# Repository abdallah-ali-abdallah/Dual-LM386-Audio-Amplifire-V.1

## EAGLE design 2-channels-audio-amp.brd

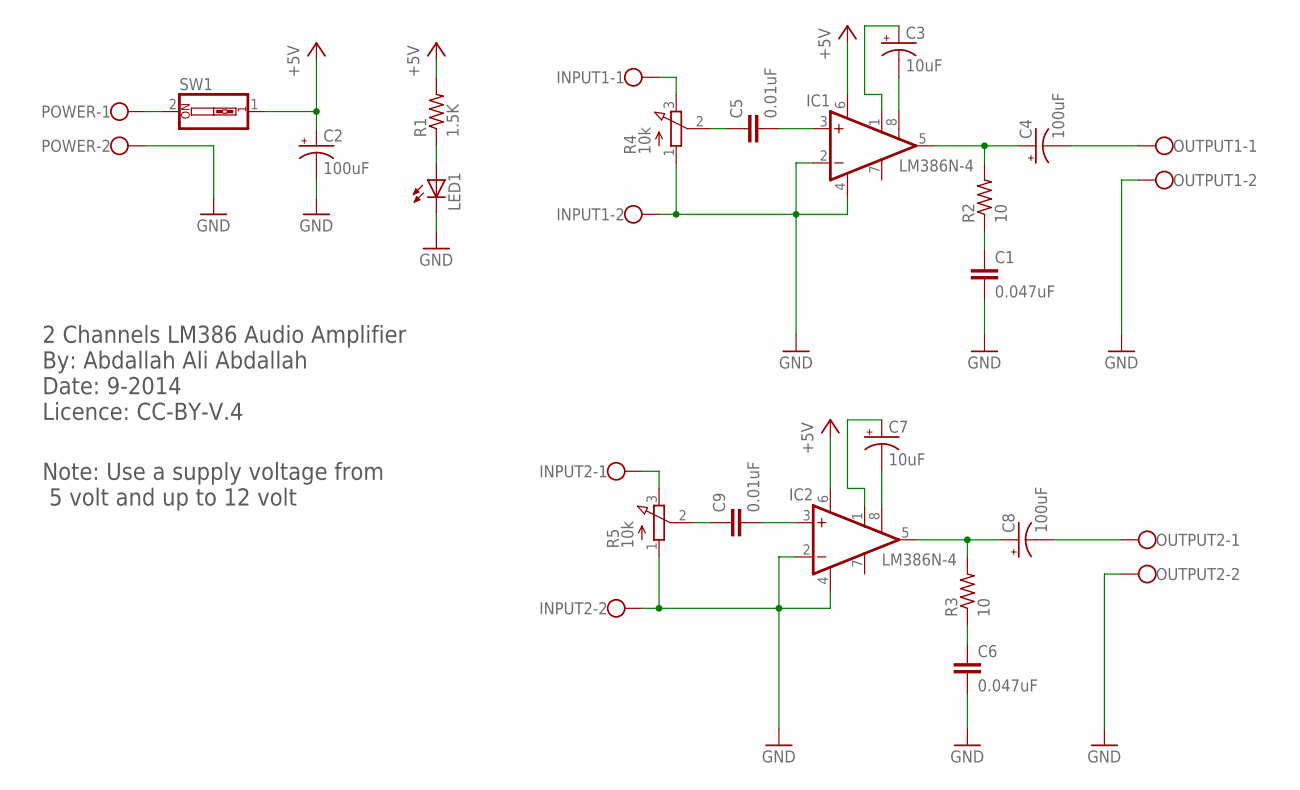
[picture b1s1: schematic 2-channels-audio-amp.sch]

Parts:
C1, C6: 0.047uF; C025-025X050
C2, C4, C8: 100uF; E2,5-6
C3, C7: 10uF; E2,5-6
C5, C9: 0.01uF; C025-025X050
IC1, IC2: LM386N-4; DIL08
INPUT1, INPUT2: W237-102
LED1: LED5MM
OUTPUT1, OUTPUT2: W237-102
POWER: W237-102
R1: 1.5K; 0204/7
R2, R3: 10; 0204/7
R4, R5: 10k; 3RP/1610N
SW1: SW_DIP-1; EDG-01

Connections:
+5V: C2.+, IC1.6 (VS), IC2.6 (VS), R1.2, SW1.1
GND: C1.2, C2.-, C6.2, IC1.2 (-IN), IC1.4 (GND), IC2.2 (-IN), IC2.4 (GND), INPUT1.2, INPUT2.2, LED1.K (C), OUTPUT1.2, OUTPUT2.2, POWER.2, R4.1 (A), R5.1 (A)
unnamed: C4.+, IC1.5 (OUT), R2.2
unnamed: C3.-, IC1.8 (GAIN)
unnamed: C3.+, IC1.1 (GAIN)
unnamed: C4.-, OUTPUT1.1
unnamed: C1.1, R2.1
unnamed: INPUT1.1, R4.3 (E)
unnamed: LED1.A, R1.1
unnamed: C5.2, IC1.3 (+IN)
unnamed: C7.-, IC2.8 (GAIN)
unnamed: C7.+, IC2.1 (GAIN)
unnamed: POWER.1, SW1.2
unnamed: C8.+, IC2.5 (OUT), R3.2
unnamed: C8.-, OUTPUT2.1
unnamed: C6.1, R3.1
unnamed: C9.2, IC2.3 (+IN)
unnamed: INPUT2.1, R5.3 (E)
unnamed: C5.1, R4.2 (S)
unnamed: C9.1, R5.2 (S)

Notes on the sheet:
2 Channels LM386 Audio Amplifier By: Abdallah Ali Abdallah Date: 9-2014 Licence: CC-BY-V.4
Note: Use a supply voltage from 5 volt and up to 12 volt

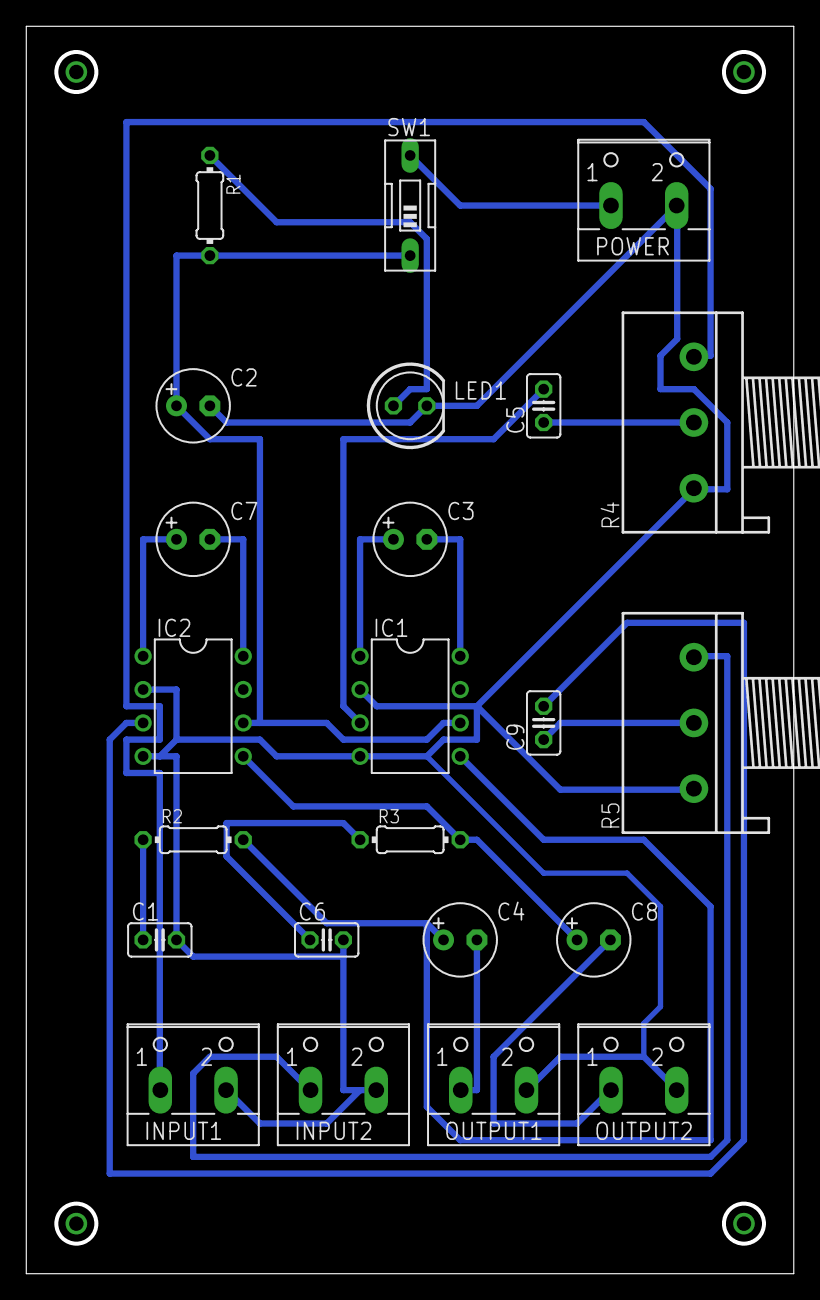
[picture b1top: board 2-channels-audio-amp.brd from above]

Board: 2 copper layers, 58.1 x 94.6 mm, 23 parts (0 on the bottom side), 20 nets.

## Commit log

2014-09-14 :tada: Added .gitattributes & .gitignore files
2014-09-14 2 Channels LM386 Audio Amplifier
    2 Channels LM386 Audio Amplifier
